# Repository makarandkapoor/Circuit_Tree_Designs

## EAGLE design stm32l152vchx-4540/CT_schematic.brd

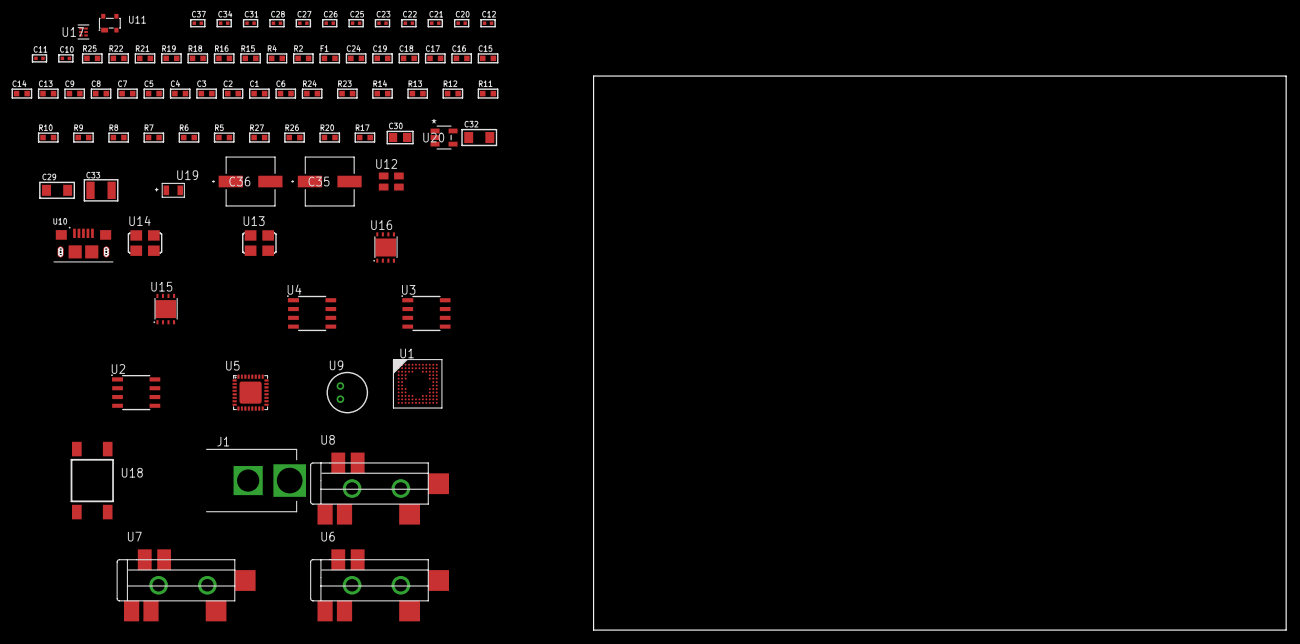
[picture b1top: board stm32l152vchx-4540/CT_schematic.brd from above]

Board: 2 copper layers, 84 parts (0 on the bottom side), 59 nets, no tracks yet.

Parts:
C1, C2, C3, C4, C5, C7: 1e-07; C0603
C6: 4.7e-06; C0603
C8: 1e-08; C0603
C9, C13, C14, C15, C16, C17, C18, C19, C24: 1e-06; C0603
C10, C11, C12, C25, C26, C27, C28, C31, C37: 1e-08; C0402
C20, C21, C22, C23, C34: 1e-07; C0402
C29, C32: 1e-05; C1206
C30: 1e-05; C0805
C33: 1e-05; C1210
C35, C36: 0.0001; EXV-9H
F1: 240.0; L0603
J1: PJ-037B; PJ-037B_PACKAGE
R2, R19, R22: 1000.0; R0603
R4: 4700.0; R0603
R5, R6, R7, R8, R9, R10, R11, R12, R13, R14, R23, R24: 10000.0; R0603
R15, R16: 1270.0; R0603
R17, R20: 100000.0; R0603
R18: 200.0; R0603
R21: 2231.0; R0603
R25: 9100.0; R0603
R26: 680000.0; R0603
R27: 120000.0; R0603
U1: STM32L152VCH6; UFBGA100
U2: AT25040B-SSHL-T; SOIC-8
U3: AT25080B-SSHL-T; SOIC-8
U4: AT25320B-SSHL-T; SOIC-8
U5: SGTL5000XNAA3; QFN-32
U6, U7, U8: SJ-43515TS-SMT-TR
U9: WM-64PCT; WM-64PC
U10: 10118193-0001LF; FCI_10118193-0001LF
U11: prtr5v0u2ax; SOT143B
U12: ASEK-32.768KHz-ECST; ASEK
U13: ASFL-24.57MHZ-NCS; ASFL1
U14: ASFL1-25MHZ-NCS; ASFL1
U15, U16: LP3878SDX-ADJ/NOPB; WSON-8
U17: TPS3895ADRYR; SON-6
U18: 4-1437565-2; SW_4-1437565-2
U19: Q65110A2395; LGM67K-G1J2-24-Z
U20: nc7sz125m5x; NC7SZ125M5X

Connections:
CLK_U1_D1: U1.D1, U12.3
CLK_U1_F1: U1.F1, U14.3
CLK_U5_21: U5.21, U13.3
GND: C1.2, C2.2, C3.2, C4.2, C5.2, C6.2, C7.2, C8.2, C9.2, C10.2, C11.2, C12.2, C20.2, C21.2, C22.2, C23.2, C24.2, C25.2, C26.2, C27.2, C28.2, C29.2, C30.2, C31.2, C32.2, C33.2, C34.2, C35.2, C36.2, C37.2, J1.2, R2.2, R5.2, R16.2, R19.2, R22.2, R25.2, R27.2, U1.D3, U1.E3, U1.F2, U1.F11, U1.F12, U1.J1, U1.K1, U2.4, U3.4, U4.4, U5.1, U5.3, U5.7, U5.EXP, U7.1, U8.1, U9.2, U10.5, U10.6, U10.7, U10.8, U10.9, U11.1, U12.2, U13.2, U14.2, U15.3, U15.PAD, U16.3, U16.PAD, U17.2, U19.C, U20.1, U20.3
NET_U1_A4: R5.1, U1.A4
NET_U1_E2: C7.1, U1.E2
NET_U1_H2: R4.1, U1.H2, U20.4
NET_U1_M1: C8.1, C9.1, F1.1, U1.L1, U1.M1
NET_U1_M12: U18.3, U18.4
NET_U2_3: R6.1, U2.3
NET_U2_7: R8.1, U2.7
NET_U3_3: R9.1, U3.3
NET_U3_7: R11.1, U3.7
NET_U4_3: R12.1, U4.3
NET_U4_7: R14.1, U4.7
NET_U5_10: C23.1, U5.10
NET_U5_29: R15.1, U5.29
NET_U5_31: R16.1, U5.31
NET_U6_1: U5.4, U6.1
NET_U6_2: U5.2, U6.2
NET_U6_5: U5.6, U6.5
NET_U7_2: C14.1, U7.2
NET_U7_5: C13.1, U7.5
NET_U8_2: C16.1, C17.1, U8.2
NET_U8_5: C15.1, U8.5
NET_U8_13: C16.2, C17.2
NET_U9_1: C18.1, C19.1, C24.1, U5.16, U9.1
NET_U9_15: C18.2, C19.2
NET_U11_4: U10.1, U11.4
NET_U15_1: C28.1, U15.1
NET_U15_6: R18.2, R19.1, U15.6
NET_U15_8: R17.1, U15.8
NET_U16_1: C31.1, U16.1
NET_U16_6: R21.2, R22.1, U16.6
NET_U16_8: R20.1, U16.8
NET_U17_1: R24.1, R25.1, U17.1
NET_U17_3: R26.2, R27.1, U17.3
NET_U17_4: R23.1, U17.4, U20.2
NET_U18_1: R2.1, U18.1, U18.2
PROC_I2S2_CK: U1.K12, U5.24
PROC_I2S2_SD: U1.K10, U5.26
PROC_I2S2_WS: U1.L12, U5.23
PROC_SPI1_MISO: U1.L4, U4.2
PROC_SPI1_MOSI: U1.C5, U4.5
PROC_SPI1_NSS: R13.1, U1.L9, U4.1
PROC_SPI1_SCK: U1.K4, U4.6
PROC_SPI2_MISO: U1.B8, U3.2
PROC_SPI2_MOSI: U1.B7, U3.5
PROC_SPI2_NSS: R10.1, U1.C9, U3.1
PROC_SPI2_SCK: U1.B9, U3.6
PROC_SPI3_MISO: U1.A7, U2.2
PROC_SPI3_MOSI: U1.B10, U2.5
PROC_SPI3_NSS: R7.1, U1.A9, U2.1
PROC_SPI3_SCK: U1.A8, U2.6
PROC_USB_DM: U1.B12, U10.2, U11.3
PROC_USB_DP: U1.A12, U10.3, U11.2
VCC_S1_10V0: C29.1, C32.1, C35.1, C36.1, J1.1, R17.2, R20.2, U15.4, U16.4
VCC_TIER1_1V2: C20.1, C30.1, R18.1, U5.30, U15.5
VCC_TIER1_3V3: C1.1, C2.1, C3.1, C4.1, C5.1, C6.1, C10.1, C11.1, C12.1, C21.1, C22.1, C25.1, C26.1, C27.1, C33.1, C34.1, C37.1, F1.2, R4.2, R6.2, R7.2, R8.2, R9.2, R10.2, R11.2, R12.2, R13.2, R14.2, R15.2, R21.1, R23.2, R24.2, R26.1, U1.C4, U1.G2, U1.G11, U1.G12, U1.H3, U2.8, U3.8, U4.8, U5.5, U5.20, U12.4, U13.4, U14.4, U16.5, U17.6, U20.5

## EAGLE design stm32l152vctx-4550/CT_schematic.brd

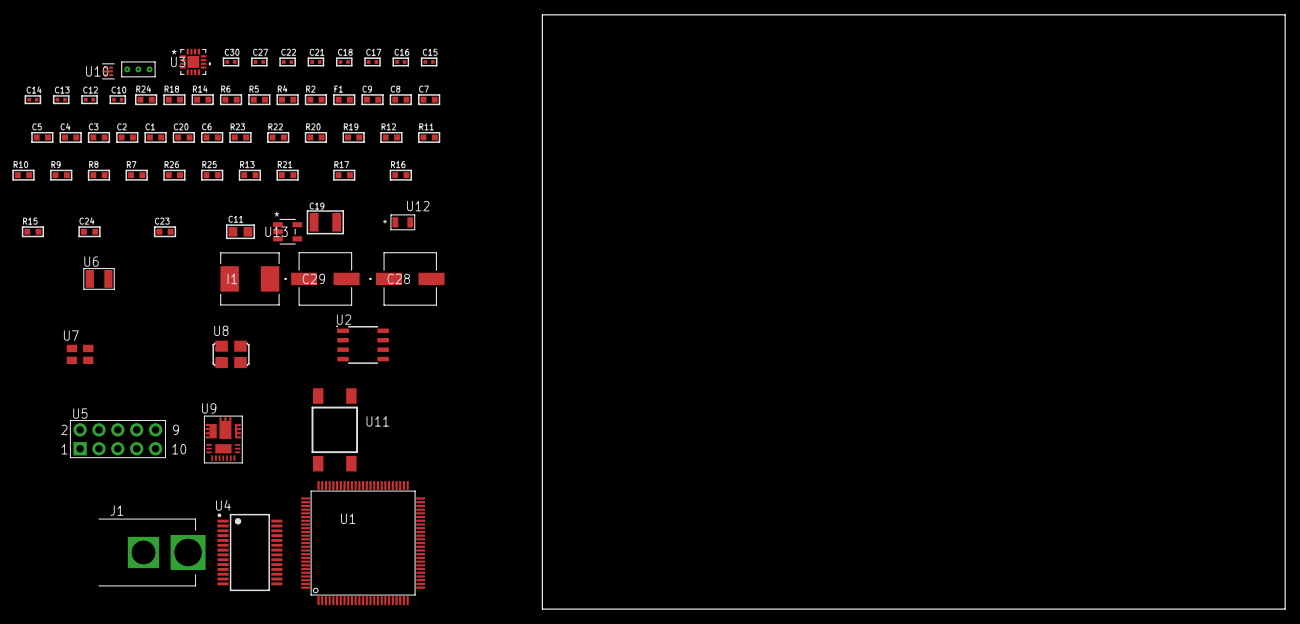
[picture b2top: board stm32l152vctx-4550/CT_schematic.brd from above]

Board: 2 copper layers, 100.0 x 80.0 mm, 69 parts (0 on the bottom side), 53 nets, no tracks yet.

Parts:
C1, C2, C3, C4, C5, C7: 1e-07; C0603
C6: 4.7e-06; C0603
C8: 1e-08; C0603
C9: 1e-06; C0603
C10, C17, C18, C30: 1e-08; C0402
C11: 4.7e-06; C0805
C12, C13, C14, C15, C16, C21, C22, C27: 1e-07; C0402
C19: 0.0001; C1210
C20: 2.2e-06; C0603
C23: 8.6971073877236e-09; R0603
C24: 2.9649229730876e-07; R0603
C28, C29: 0.0001; EXV-9H
F1: 240.0; L0603
I1: 6.8e-07; IND25X25CZ
J1: PJ-037B; PJ-037B_PACKAGE
R2: 1000.0; R0603
R4: 4700.0; R0603
R5, R6: 2200.0; R0603
R7, R8, R9, R10, R11, R12, R22, R23: 10000.0; R0603
R13: 100000.0; R0603
R14: 0.1; R0603
R15: 4030.2416170974; R0603
R16: 719.68600305311; R0603
R17: 58.613333333333; R0603
R18: 130.0; R0603
R19: 39000.0; R0603
R20: 49900.0; R0603
R21: 5147.5789473684; R0603
R24: 9100.0; R0603
R25: 680000.0; R0603
R26: 120000.0; R0603
U1: STM32L152VCT6; LQFP100
U2: AT25080B-SSHL-T; SOIC-8
U3: M41T65Q6F; M41T65_QFN-16
U4: ST3241EBPR; SSOP-28
U5: HTSS-105-01-G-D
U6: ABS07-32.768KHZ-7-T
U7: ASEK-32.768KHz-ECST; ASEK
U8: ASFL1-25MHZ-NCS; ASFL1
U9: IR3899MTR1PBF
U10: TPS3895ADRYR; SON-6
U11: 4-1437565-2; SW_4-1437565-2
U12: Q65110A2395; LGM67K-G1J2-24-Z
U13: nc7sz125m5x; NC7SZ125M5X
U14: Dummy; DUMMY_PACKAGE_141

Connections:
CLK_CRYSTAL_U3_1: U3.1, U6.1
CLK_CRYSTAL_U3_2: U3.2, U6.2
CLK_U1_8: U1.8, U7.3
CLK_U1_12: U1.12, U8.3
GND: C1.2, C2.2, C3.2, C4.2, C5.2, C6.2, C7.2, C8.2, C9.2, C10.2, C11.2, C12.2, C15.2, C16.2, C17.2, C18.2, C20.2, C21.2, C22.2, C27.2, C28.2, C29.2, C30.2, J1.2, R2.2, R7.2, R14.1, R14.2, R16.2, R19.2, R21.2, R24.2, R26.2, U1.10, U1.19, U1.20, U1.27, U1.49, U1.74, U1.99, U2.4, U3.3, U3.5, U3.17, U4.23, U4.25, U5.9, U7.2, U8.2, U9.4, U9.11, U9.17, U10.2, U12.C, U13.1, U13.3, U14.1
NET_U1_6: C7.1, U1.6
NET_U1_14: R4.1, U1.14, U13.4
NET_U1_22: C8.1, C9.1, F1.1, U1.21, U1.22
NET_U1_92: R5.1, U1.92, U3.10
NET_U1_93: R6.1, U1.93, U3.9
NET_U1_94: R7.1, U1.94
NET_U1_98: U11.3, U11.4
NET_U2_3: R8.1, U2.3
NET_U2_7: R10.1, U2.7
NET_U3_4: R11.1, U3.4
NET_U3_11: R12.1, U3.11
NET_U4_1: C14.1, U4.1
NET_U4_2: C14.2, U4.2
NET_U4_3: C16.1, U4.3
NET_U4_22: R13.1, U4.22
NET_U4_24: C13.2, U4.24
NET_U4_27: C15.1, U4.27
NET_U4_28: C13.1, U4.28
NET_U5_3: U4.4, U5.3
NET_U5_4: U4.5, U5.4
NET_U5_5: U4.9, U5.5
NET_U5_6: U4.10, U5.6
NET_U9_1: C23.1, R15.1, R16.1, R17.1, R18.1, U9.1, U9.8
NET_U9_2: C22.1, U9.2
NET_U9_3: C23.2, C24.1, C24.2, U9.3
NET_U9_5: R19.1, U9.5
NET_U9_10: C20.1, U9.10
NET_U9_12: C19.1, I1.1, U9.12
NET_U9_14: C19.2, U9.14
NET_U9_15: R20.1, R21.1, U9.15
NET_U9_ATNET_3: I1.2, R15.2
NET_U9_ATNET_4: C24.2, R17.2
NET_U10_1: R23.1, R24.1, U10.1
NET_U10_3: R25.2, R26.1, U10.3
NET_U10_4: R22.1, U10.4, U13.2
NET_U11_1: R2.1, U11.1, U11.2
PROC_PE2: U1.1, U14.2
PROC_PE3: U1.2, U14.3
PROC_SPI1_MISO: U1.31, U2.2
PROC_SPI1_MOSI: U1.32, U2.5
PROC_SPI1_NSS: R9.1, U1.29, U2.1
PROC_SPI1_SCK: U1.30, U2.6
PROC_USART1_CTS: U1.70, U4.13
PROC_USART1_RTS: U1.71, U4.18
PROC_USART1_RX: U1.69, U4.19
PROC_USART1_TX: U1.68, U4.14
VCC_S1_16V8: C21.1, C28.1, C29.1, J1.1, R20.2, U9.9
VCC_TIER1_3V3: C1.1, C2.1, C3.1, C4.1, C5.1, C6.1, C10.1, C11.1, C12.1, C17.1, C18.1, C27.1, C30.1, F1.2, I1.2, R4.2, R5.2, R6.2, R8.2, R9.2, R10.2, R11.2, R12.2, R13.2, R15.2, R22.2, R23.2, R25.1, U1.11, U1.28, U1.50, U1.75, U1.100, U2.8, U3.14, U4.26, U7.4, U8.4, U10.6, U13.5

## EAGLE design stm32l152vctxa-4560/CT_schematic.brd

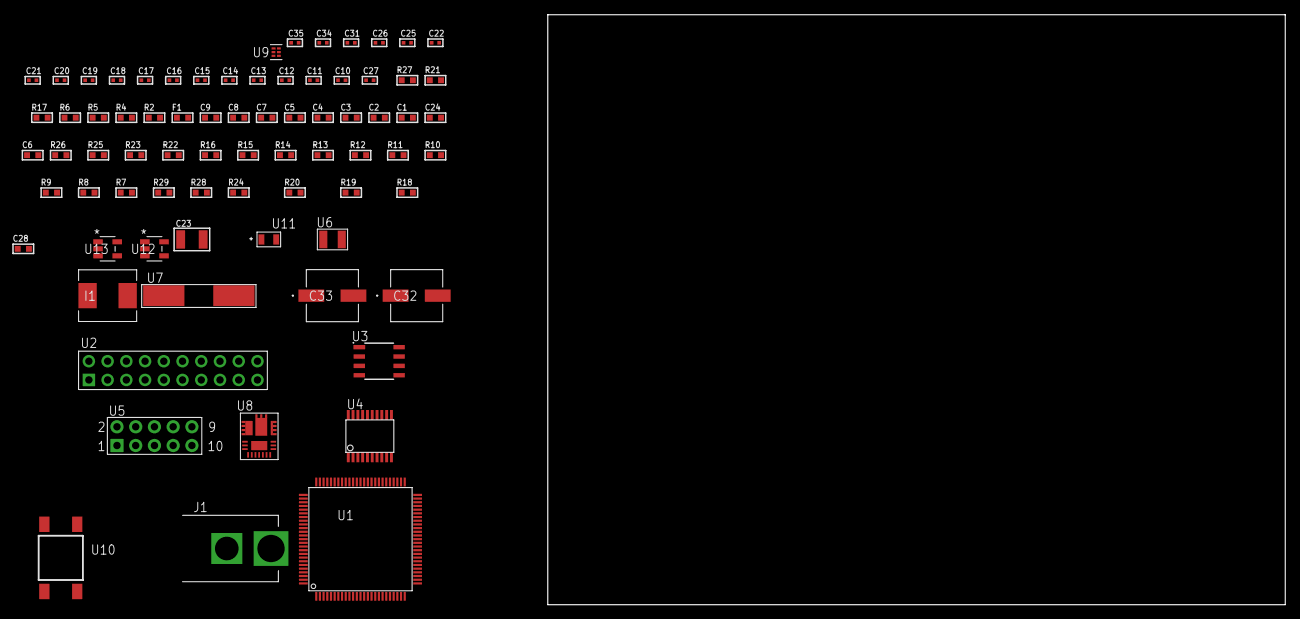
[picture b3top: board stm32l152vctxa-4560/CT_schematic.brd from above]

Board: 2 copper layers, 100.0 x 80.0 mm, 76 parts (0 on the bottom side), 52 nets, no tracks yet.

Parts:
C1, C2, C3, C4, C5, C7: 1e-07; C0603
C6: 4.7e-06; C0603
C8: 1e-08; C0603
C9: 1e-06; C0603
C10, C11, C12, C13: 1e-11; C0402
C14, C15, C17, C18, C19, C20, C21, C22, C25, C26, C31: 1e-07; C0402
C16, C34, C35: 1e-08; C0402
C23: 0.0001; C1210
C24: 2.2e-06; C0603
C27: 8.2e-09; C0402
C28: 2.724074888439e-07; R0603
C32, C33: 0.0001; EXV-9H
F1: 240.0; L0603
I1: 6.8e-07; IND25X25CZ
J1: PJ-037B; PJ-037B_PACKAGE
R2: 1000.0; R0603
R4: 4700.0; R0603
R5, R6: 2200.0; R0603
R7, R8, R9, R10, R11, R12, R13, R14, R15, R16, R25, R26: 10000.0; R0603
R17: 0.1; R0603
R18: 4030.2416170974; R0603
R19: 719.68600305311; R0603
R20: 63.795609756098; R0603
R21: 130.0; R0603
R22: 39000.0; R0603
R23: 49900.0; R0603
R24: 5286.7027027027; R0603
R27: 9100.0; R0603
R28: 680000.0; R0603
R29: 120000.0; R0603
U1: STM32L152VCT6A; LQFP100
U2: TST-110-05-T-D-RA
U3: 24AA1025T-I/SN; SOIC-8
U4: SP3203ECY-L/TR; TSSOP20-I
U5: HTSS-105-01-G-D
U6: ABS07-32.768KHZ-7-T
U7: ABLS-25.000MHZ-B2F-T
U8: IR3899MTR1PBF
U9: TPS3895ADRYR; SON-6
U10: 4-1437565-2; SW_4-1437565-2
U11: Q65110A2395; LGM67K-G1J2-24-Z
U12, U13: nc7sz125m5x; NC7SZ125M5X

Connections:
CLK_CRYSTAL_U1_8: C10.1, U1.8, U6.1
CLK_CRYSTAL_U1_9: C11.1, U1.9, U6.2
CLK_CRYSTAL_U1_12: C12.1, U1.12, U7.1
CLK_CRYSTAL_U1_13: C13.1, U1.13, U7.2
GND: C1.2, C2.2, C3.2, C4.2, C5.2, C6.2, C7.2, C8.2, C9.2, C10.2, C11.2, C12.2, C13.2, C14.2, C15.2, C16.2, C17.2, C18.2, C21.2, C22.2, C24.2, C25.2, C26.2, C31.2, C32.2, C33.2, C34.2, C35.2, J1.2, R2.2, R7.2, R13.2, R16.2, R17.1, R17.2, R19.2, R22.2, R24.2, R27.2, R29.2, U1.10, U1.19, U1.20, U1.27, U1.49, U1.74, U1.99, U2.4, U2.6, U2.8, U2.10, U2.12, U2.14, U2.16, U2.18, U2.20, U3.4, U3.7, U4.18, U5.9, U8.4, U8.11, U8.17, U9.2, U11.C, U12.2, U12.3, U13.1, U13.3
NET_U1_6: C7.1, U1.6
NET_U1_14: R4.1, U1.14, U13.4
NET_U1_22: C8.1, C9.1, F1.1, U1.21, U1.22
NET_U1_92: R5.1, U1.92, U3.6
NET_U1_93: R6.1, U1.93, U3.5
NET_U1_94: R7.1, U1.94
NET_U1_98: U10.3, U10.4
NET_U2_19: R13.1, U2.19
NET_U3_1: R15.1, U3.1
NET_U3_2: R16.1, U3.2
NET_U3_3: R14.1, U3.3
NET_U4_1: C19.1, U4.1
NET_U4_2: C21.1, U4.2
NET_U4_3: C19.2, U4.3
NET_U4_4: C20.1, U4.4
NET_U4_5: C20.2, U4.5
NET_U4_6: C22.1, U4.6
NET_U5_3: U4.14, U5.3
NET_U5_4: U4.13, U5.4
NET_U5_5: U4.17, U5.5
NET_U5_6: U4.16, U5.6
NET_U8_1: C27.1, R18.1, R19.1, R20.1, R21.1, U8.1, U8.8
NET_U8_2: C26.1, U8.2
NET_U8_3: C27.2, C28.1, C28.2, U8.3
NET_U8_5: R22.1, U8.5
NET_U8_10: C24.1, U8.10
NET_U8_12: C23.1, I1.1, U8.12
NET_U8_14: C23.2, U8.14
NET_U8_15: R23.1, R24.1, U8.15
NET_U8_ATNET_3: I1.2, R18.2
NET_U8_ATNET_4: C28.2, R20.2
NET_U9_1: R26.1, R27.1, U9.1
NET_U9_3: R28.2, R29.1, U9.3
NET_U9_4: R25.1, U9.4, U12.4, U13.2
NET_U10_1: R2.1, U10.1, U10.2
PROC_SYS_JTCK_SWCLK: R11.1, U1.76, U2.9
PROC_SYS_JTDI: R9.1, U1.77, U2.5
PROC_SYS_JTDO_TRACESWO: U1.89, U2.13
PROC_SYS_JTMS_SWDIO: R10.1, U1.72, U2.7
PROC_SYS_JTRST: R8.1, U1.90, U2.3
PROC_USART1_CTS: U1.70, U4.8
PROC_USART1_RTS: U1.71, U4.10
PROC_USART1_RX: U1.69, U4.11
PROC_USART1_TX: U1.68, U4.7
RST_OUT_U2_SRESET_B: R12.1, U2.15, U12.1
VCC_S1_16V4: C25.1, C32.1, C33.1, J1.1, R23.2, U8.9
VCC_TIER1_3V3: C1.1, C2.1, C3.1, C4.1, C5.1, C6.1, C14.1, C15.1, C16.1, C17.1, C18.1, C31.1, C34.1, C35.1, F1.2, I1.2, R4.2, R5.2, R6.2, R8.2, R9.2, R10.2, R11.2, R12.2, R14.2, R15.2, R18.2, R25.2, R26.2, R28.1, U1.11, U1.28, U1.50, U1.75, U1.100, U2.1, U2.2, U3.8, U4.12, U4.19, U9.6, U12.5, U13.5

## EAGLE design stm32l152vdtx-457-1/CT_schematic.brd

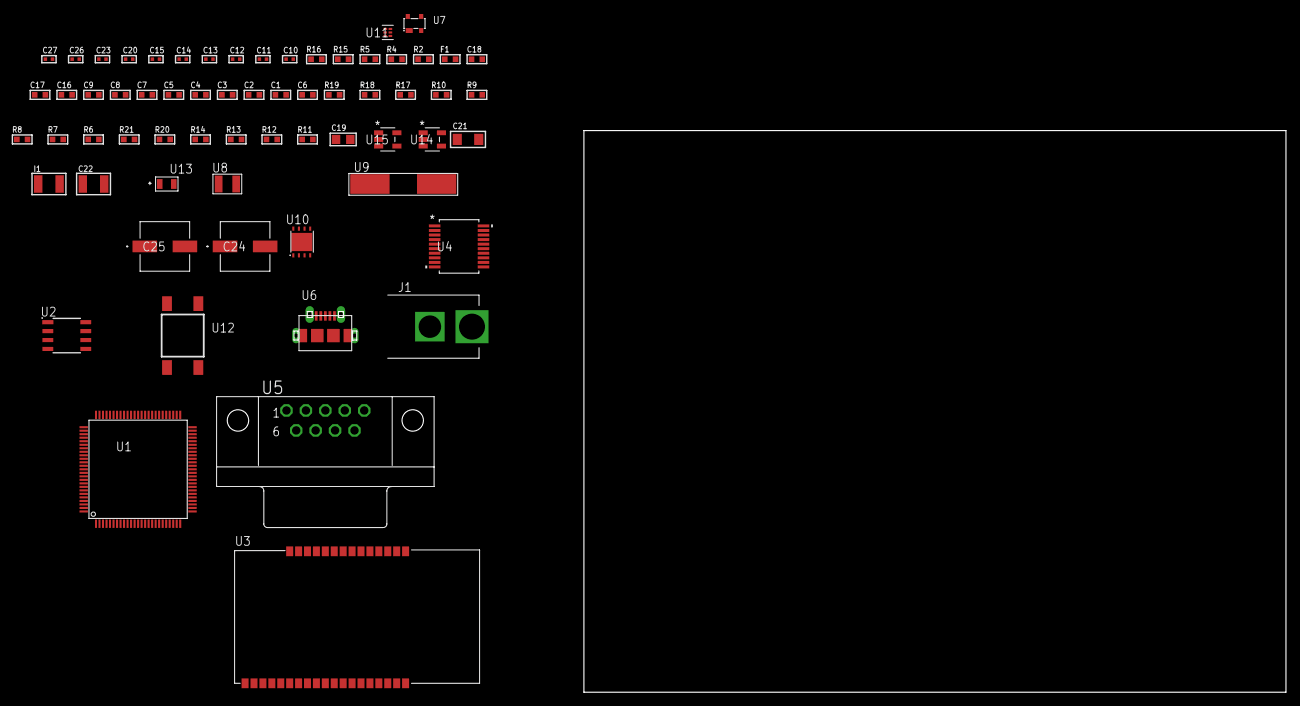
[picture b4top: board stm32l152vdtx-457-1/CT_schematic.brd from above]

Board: 2 copper layers, 64 parts (0 on the bottom side), 46 nets, no tracks yet.

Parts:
C1, C2, C3, C4, C5, C7: 1e-07; C0603
C6: 4.7e-06; C0603
C8: 1e-08; C0603
C9, C16, C17, C18: 1e-06; C0603
C10, C11, C12, C13: 1e-11; C0402
C14, C20, C26, C27: 1e-08; C0402
C15, C23: 1e-07; C0402
C19: 4.7e-06; C0805
C21: 1e-05; C1206
C22: 1e-05; C1210
C24, C25: 0.0001; EXV-9H
F1: 240.0; L0603
I1: 1.5e-05; L1210
J1: PJ-037B; PJ-037B_PACKAGE
R2, R16: 1000.0; R0603
R4, R5: 4700.0; R0603
R6, R7, R8, R9, R10, R17, R18: 10000.0; R0603
R11, R12, R13, R14: 100000.0; R0603
R15: 1500.0; R0603
R19: 18000.0; R0603
R20: 470000.0; R0603
R21: 120000.0; R0603
U1: STM32L152VDT6; LQFP100
U2: AT25080B-SSHL-T; SOIC-8
U3: ETRX3587
U4: MAX3218EAP+T; SSOP-20
U5: 182-009-113R531; 182-009-MALE
U6: 47590-0001; MICRO_USB_AB
U7: prtr5v0u2ax; SOT143B
U8: ABS07-32.768KHZ-7-T
U9: ABLS-25.000MHZ-B2F-T
U10: LP3878SDX-ADJ/NOPB; WSON-8
U11: TPS3895ADRYR; SON-6
U12: 4-1437565-2; SW_4-1437565-2
U13: Q65110A2395; LGM67K-G1J2-24-Z
U14, U15: nc7sz125m5x; NC7SZ125M5X

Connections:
CLK_CRYSTAL_U1_8: C10.1, U1.8, U8.1
CLK_CRYSTAL_U1_9: C11.1, U1.9, U8.2
CLK_CRYSTAL_U1_12: C12.1, U1.12, U9.1
CLK_CRYSTAL_U1_13: C13.1, U1.13, U9.2
GND: C1.2, C2.2, C3.2, C4.2, C5.2, C6.2, C7.2, C8.2, C9.2, C10.2, C11.2, C12.2, C13.2, C14.2, C15.2, C16.2, C17.2, C18.2, C20.2, C21.2, C22.2, C23.2, C24.2, C25.2, C26.2, C27.2, J1.2, R2.2, R6.2, R10.2, R16.2, R19.2, R21.2, U1.10, U1.19, U1.20, U1.27, U1.49, U1.74, U1.99, U2.4, U3.1, U3.13, U3.19, U3.20, U3.31, U3.33, U4.5, U4.17, U4.20, U5.5, U6.5, U6.6, U6.7, U6.8, U6.9, U7.1, U10.3, U10.PAD, U11.2, U13.C, U14.1, U14.3, U15.1, U15.3
NET_U1_6: C7.1, U1.6
NET_U1_14: R5.1, U1.14, U15.4
NET_U1_22: C8.1, C9.1, F1.1, U1.21, U1.22
NET_U1_94: R6.1, U1.94
NET_U1_98: U12.3, U12.4
NET_U2_3: R7.1, U2.3
NET_U2_7: R9.1, U2.7
NET_U3_7: R4.1, U3.7, U14.4
NET_U3_21: R10.1, U3.21
NET_U4_1: I1.1, U4.1
NET_U4_2: R11.1, U4.2
NET_U4_3: R12.1, U4.3
NET_U4_4: R13.1, U4.4
NET_U4_15: C18.1, U4.15
NET_U4_16: C19.2, U4.16
NET_U4_18: C19.1, U4.18
NET_U4_19: C17.1, U4.19
NET_U5_2: U4.12, U5.2
NET_U5_3: U4.14, U5.3
NET_U5_7: U4.11, U5.7
NET_U5_8: U4.13, U5.8
NET_U7_4: U6.1, U7.4
NET_U10_1: C20.1, U10.1
NET_U10_6: R15.2, R16.1, U10.6
NET_U10_8: R14.1, U10.8
NET_U11_1: R18.1, R19.1, U11.1
NET_U11_3: R20.2, R21.1, U11.3
NET_U11_4: R17.1, U11.4, U14.2, U15.2
NET_U12_1: R2.1, U12.1, U12.2
PROC_SPI1_MISO: U1.31, U2.2
PROC_SPI1_MOSI: U1.32, U2.5
PROC_SPI1_NSS: R8.1, U1.29, U2.1
PROC_SPI1_SCK: U1.30, U2.6
PROC_UART4_RX: U1.79, U3.17
PROC_UART4_TX: U1.78, U3.18
PROC_UART5_RX: U1.83, U4.9
PROC_UART5_TX: U1.80, U4.7
PROC_USB_DM: U1.70, U6.2, U7.3
PROC_USB_DP: U1.71, U6.3, U7.2
VCC_S1_11V1: C21.1, C24.1, C25.1, J1.1, R14.2, U10.4
VCC_TIER1_2V5: C1.1, C2.1, C3.1, C4.1, C5.1, C6.1, C14.1, C15.1, C16.1, C22.1, C23.1, C26.1, C27.1, F1.2, I1.2, R4.2, R5.2, R7.2, R8.2, R9.2, R11.2, R12.2, R13.2, R15.1, R17.2, R18.2, R20.1, U1.11, U1.28, U1.50, U1.75, U1.100, U2.8, U3.32, U4.6, U10.5, U11.6, U14.5, U15.5

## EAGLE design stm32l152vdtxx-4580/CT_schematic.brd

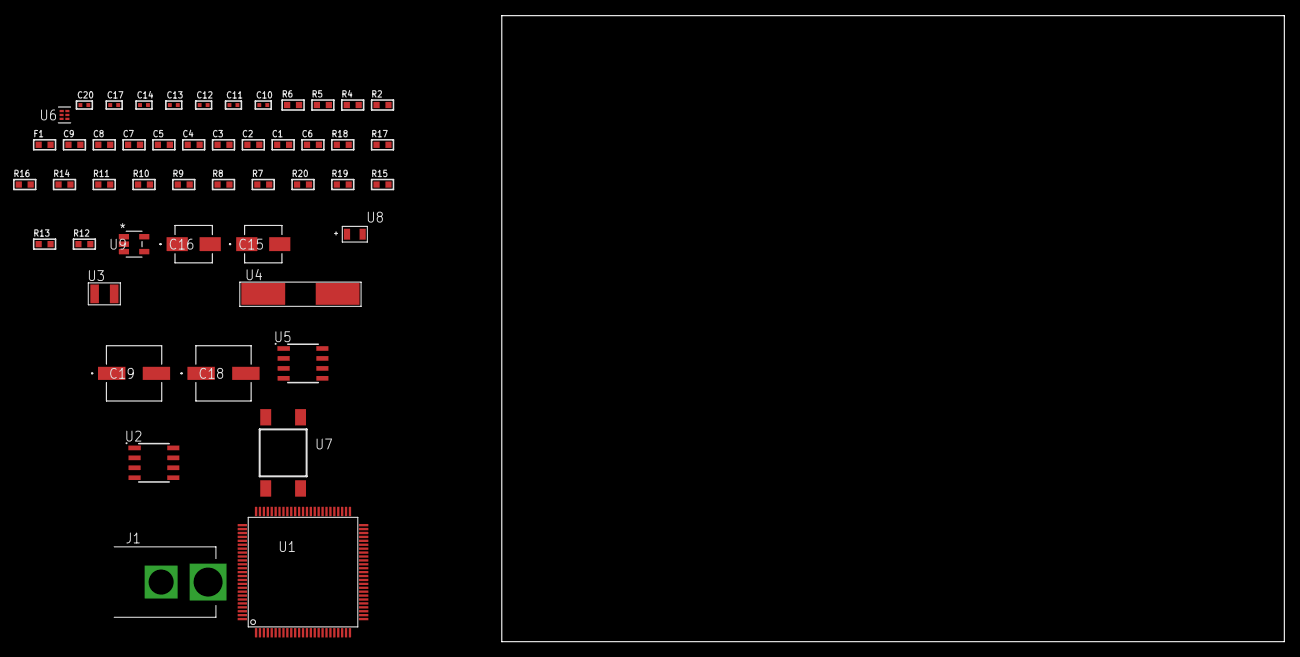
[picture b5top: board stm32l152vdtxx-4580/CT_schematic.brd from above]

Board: 2 copper layers, 100.0 x 80.0 mm, 49 parts (0 on the bottom side), 25 nets, no tracks yet.

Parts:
C1, C2, C3, C4, C5, C7: 1e-07; C0603
C6: 4.7e-06; C0603
C8: 1e-08; C0603
C9: 1e-06; C0603
C10, C11, C12, C13: 1e-11; C0402
C14, C20: 1e-08; C0402
C15: 1e-06; EXV-9B
C16: 2.2e-06; EXV-9B
C17: 1e-07; C0402
C18, C19: 0.0001; EXV-9H
F1: 240.0; L0603
J1: PJ-037B; PJ-037B_PACKAGE
R2: 1000.0; R0603
R4: 4700.0; R0603
R5, R6: 2200.0; R0603
R7, R8, R9, R10, R11, R16, R17: 10000.0; R0603
R12, R13, R15: 100000.0; R0603
R14: 47000.0; R0603
R18: 82000.0; R0603
R19: 300000.0; R0603
R20: 120000.0; R0603
U1: STM32L152VDT6X; LQFP100
U2: AT24C02D-SSHM-T; AT24C02D
U3: ABS07-32.768KHZ-7-T
U4: ABLS-25.000MHZ-B2F-T
U5: LP2954AIMX/NOPB; LP2954
U6: TPS3895ADRYR; SON-6
U7: 4-1437565-2; SW_4-1437565-2
U8: Q65110A2395; LGM67K-G1J2-24-Z
U9: nc7sz125m5x; NC7SZ125M5X

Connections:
CLK_CRYSTAL_U1_8: C10.1, U1.8, U3.1
CLK_CRYSTAL_U1_9: C11.1, U1.9, U3.2
CLK_CRYSTAL_U1_12: C12.1, U1.12, U4.1
CLK_CRYSTAL_U1_13: C13.1, U1.13, U4.2
GND: C1.2, C2.2, C3.2, C4.2, C5.2, C6.2, C7.2, C8.2, C9.2, C10.2, C11.2, C12.2, C13.2, C14.2, C15.2, C16.2, C17.2, C18.2, C19.2, C20.2, J1.2, R2.2, R7.2, R8.2, R10.2, R11.2, R15.2, R18.2, R20.2, U1.10, U1.19, U1.20, U1.27, U1.49, U1.74, U1.99, U2.4, U5.4, U6.2, U8.C, U9.1, U9.3
NET_U1_6: C7.1, U1.6
NET_U1_14: R4.1, U1.14, U9.4
NET_U1_22: C8.1, C9.1, F1.1, U1.21, U1.22
NET_U1_92: R5.1, U1.92, U2.6
NET_U1_93: R6.1, U1.93, U2.5
NET_U1_94: R7.1, U1.94
NET_U1_98: U7.3, U7.4
NET_U2_1: R9.1, U2.1
NET_U2_2: R10.1, U2.2
NET_U2_3: R11.1, U2.3
NET_U2_7: R8.1, U2.7
NET_U5_3: R13.1, U5.3
NET_U5_5: R12.1, U5.5
NET_U5_7: R14.2, R15.1, U5.7
NET_U6_1: R17.1, R18.1, U6.1
NET_U6_3: R19.2, R20.1, U6.3
NET_U6_4: R16.1, U6.4, U9.2
NET_U7_1: R2.1, U7.1, U7.2
VCC_S1_12V3: C15.1, C18.1, C19.1, J1.1, R13.2, U5.8
VCC_TIER1_1V8: C1.1, C2.1, C3.1, C4.1, C5.1, C6.1, C14.1, C16.1, C17.1, C20.1, F1.2, R4.2, R5.2, R6.2, R9.2, R12.2, R14.1, R16.2, R17.2, R19.1, U1.11, U1.28, U1.50, U1.75, U1.100, U2.8, U5.1, U6.6, U9.5

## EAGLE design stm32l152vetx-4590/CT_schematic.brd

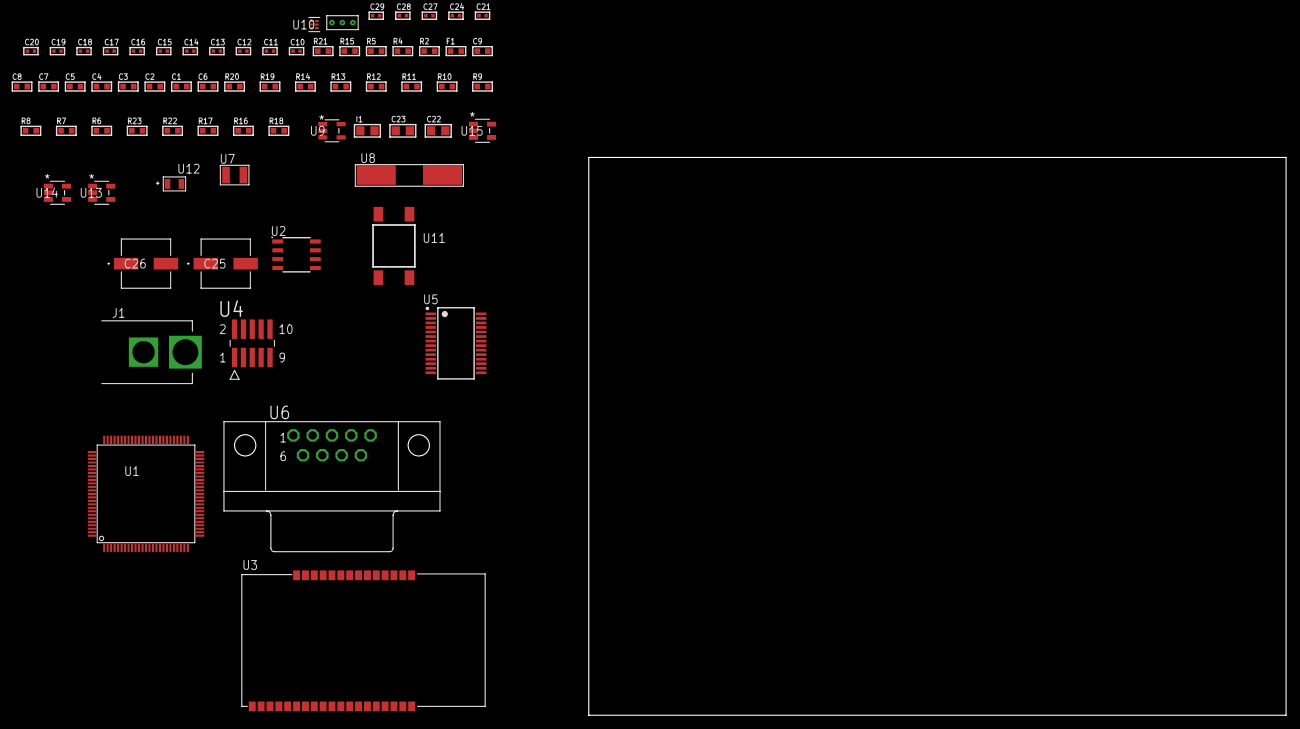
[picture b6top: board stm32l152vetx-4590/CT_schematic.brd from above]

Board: 2 copper layers, 100.0 x 80.0 mm, 69 parts (0 on the bottom side), 50 nets, no tracks yet.

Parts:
C1, C2, C3, C4, C5, C7: 1e-07; C0603
C6: 4.7e-06; C0603
C8: 1e-08; C0603
C9: 1e-06; C0603
C10, C11, C12, C13: 1e-11; C0402
C14, C27, C28, C29: 1e-08; C0402
C15, C16, C17, C18, C19, C20, C21, C24: 1e-07; C0402
C22, C23: 1e-05; C0805
C25, C26: 0.0001; EXV-9H
F1: 240.0; L0603
I1: 1e-05; L0805
J1: PJ-037B; PJ-037B_PACKAGE
R2: 1000.0; R0603
R4, R5: 4700.0; R0603
R6, R7, R8, R9, R10, R11, R12, R13, R14, R19, R20: 10000.0; R0603
R15: 5.0; R0603
R16: 100000.0; R0603
R17: 220000.0; R0603
R18: 1000000.0; R0603
R21: 9100.0; R0603
R22: 680000.0; R0603
R23: 120000.0; R0603
U1: STM32L152VET6; LQFP100
U2: AT25512N-SH-T; SOIC-8
U3: ETRX3587
U4: FTSH-105-01-L-DV-K; SAMTEC_FTSH-105-01-L-DV-K
U5: ST3241EBPR; SSOP-28
U6: 182-009-113R531; 182-009-MALE
U7: ABS07-32.768KHZ-7-T
U8: ABLS-25.000MHZ-B2F-T
U9: ltc3406es5; TSOT-23-5
U10: TPS3895ADRYR; SON-6
U11: 4-1437565-2; SW_4-1437565-2
U12: Q65110A2395; LGM67K-G1J2-24-Z
U13, U14, U15: nc7sz125m5x; NC7SZ125M5X
U16: Dummy; DUMMY_PACKAGE_146

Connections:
CLK_CRYSTAL_U1_8: C10.1, U1.8, U7.1
CLK_CRYSTAL_U1_9: C11.1, U1.9, U7.2
CLK_CRYSTAL_U1_12: C12.1, U1.12, U8.1
CLK_CRYSTAL_U1_13: C13.1, U1.13, U8.2
GND: C1.2, C2.2, C3.2, C4.2, C5.2, C6.2, C7.2, C8.2, C9.2, C10.2, C11.2, C12.2, C13.2, C14.2, C15.2, C16.2, C17.2, C20.2, C21.2, C22.2, C23.1, C23.2, C24.2, C25.2, C26.2, C27.2, C28.2, C29.2, J1.2, R2.2, R6.2, R10.2, R14.2, R15.2, R17.2, R21.2, R23.2, U1.10, U1.19, U1.20, U1.27, U1.49, U1.74, U1.99, U2.4, U3.1, U3.13, U3.19, U3.20, U3.31, U3.33, U4.3, U4.5, U5.23, U5.25, U6.5, U9.2, U10.2, U12.C, U13.2, U13.3, U14.1, U14.3, U15.1, U15.3, U16.1
NET_U1_6: C7.1, U1.6
NET_U1_14: R5.1, U1.14, U15.4
NET_U1_22: C8.1, C9.1, F1.1, U1.21, U1.22
NET_U1_94: R6.1, U1.94
NET_U1_98: U11.3, U11.4
NET_U2_3: R7.1, U2.3
NET_U2_7: R9.1, U2.7
NET_U3_7: R4.1, U3.7, U14.4
NET_U3_21: R10.1, U3.21
NET_U4_9: R15.1, U4.9
NET_U5_1: C19.1, U5.1
NET_U5_2: C19.2, U5.2
NET_U5_3: C21.1, U5.3
NET_U5_22: R16.1, U5.22
NET_U5_24: C18.2, U5.24
NET_U5_27: C20.1, U5.27
NET_U5_28: C18.1, U5.28
NET_U6_2: U5.4, U6.2
NET_U6_3: U5.9, U6.3
NET_U6_7: U5.5, U6.7
NET_U6_8: U5.10, U6.8
NET_U9_3: I1.1, U9.3
NET_U9_5: R17.1, R18.1, U9.5
NET_U9_ATNET_3: I1.2, R18.2
NET_U10_1: R20.1, R21.1, U10.1
NET_U10_3: R22.2, R23.1, U10.3
NET_U10_4: R19.1, U10.4, U13.4, U14.2, U15.2
NET_U11_1: R2.1, U11.1, U11.2
PROC_SPI1_MISO: U1.31, U2.2
PROC_SPI1_MOSI: U1.32, U2.5
PROC_SPI1_NSS: R8.1, U1.29, U2.1
PROC_SPI1_SCK: U1.30, U2.6
PROC_SYS_JTCK_SWCLK: R14.1, U1.76, U4.4
PROC_SYS_JTDI: R12.1, U1.77, U4.8
PROC_SYS_JTDO_TRACESWO: U1.89, U4.6
PROC_SYS_JTMS_SWDIO: R13.1, U1.72, U4.2
PROC_TIM2_CH1: U1.23, U16.3
PROC_TIM2_CH3: U1.25, U16.2
PROC_UART4_RX: U1.79, U3.17
PROC_UART4_TX: U1.78, U3.18
PROC_UART5_RX: U1.83, U5.19
PROC_UART5_TX: U1.80, U5.14
RST_OUT_U4_JTAG_RST_B: R11.1, U4.10, U13.1
VCC_S1_5V4: C22.1, C25.1, C26.1, J1.1, U9.4
VCC_TIER1_3V3: C1.1, C2.1, C3.1, C4.1, C5.1, C6.1, C14.1, C15.1, C16.1, C17.1, C23.2, C24.1, C27.1, C28.1, C29.1, F1.2, I1.2, R4.2, R5.2, R7.2, R8.2, R9.2, R11.2, R12.2, R13.2, R16.2, R18.2, R19.2, R20.2, R22.1, U1.11, U1.28, U1.50, U1.75, U1.100, U2.8, U3.32, U4.1, U5.26, U10.6, U13.5, U14.5, U15.5

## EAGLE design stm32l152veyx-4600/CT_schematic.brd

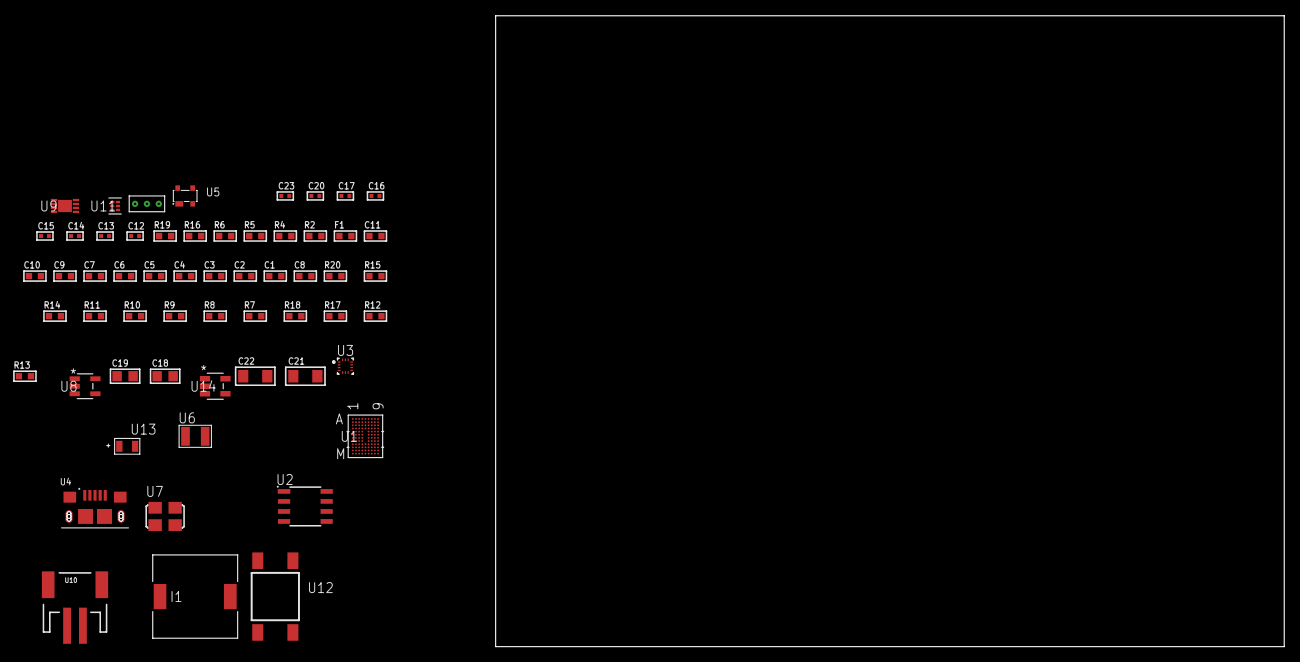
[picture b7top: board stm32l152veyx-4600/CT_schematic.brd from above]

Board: 2 copper layers, 154.3 x 80.0 mm, 58 parts (0 on the bottom side), 33 nets, no tracks yet.

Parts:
C1, C2, C3, C4, C5, C6, C7, C9: 1e-07; C0603
C8: 4.7e-06; C0603
C10: 1e-08; C0603
C11: 1e-06; C0603
C12, C13: 1e-11; C0402
C14, C17, C23: 1e-08; C0402
C15, C16, C20: 1e-07; C0402
C18, C19: 1e-05; C0805
C21, C22: 1e-05; C1206
F1: 240.0; L0603
I1: 3.8e-06; DR1040
R2: 1000.0; R0603
R4: 4700.0; R0603
R5, R6: 2200.0; R0603
R7, R8, R9, R10, R11, R14, R15, R20: 10000.0; R0603
R12: 220000.0; R0603
R13: 1000000.0; R0603
R16: 9100.0; R0603
R17: 680000.0; R0603
R18: 120000.0; R0603
R19: 2000.0; R0603
U1: STM32L152VEY6TR; WLCSP104
U2: AT25080B-SSHL-T; SOIC-8
U3: BMC150; LGA14R35P5X6_200X200X100
U4: 10118193-0001LF; FCI_10118193-0001LF
U5: prtr5v0u2ax; SOT143B
U6: ABS07-32.768KHZ-7-T
U7: ASFL1-25MHZ-NCS; ASFL1
U8: ltc3406es5; TSOT-23-5
U9: MCP73831T-2ACI/MC; DFN8_2X3MC
U10: S2B-PH-SM4-TB(LF)(SN); JST-2-SMD
U11: TPS3895ADRYR; SON-6
U12: 4-1437565-2; SW_4-1437565-2
U13: Q65110A2395; LGM67K-G1J2-24-Z
U14: nc7sz125m5x; NC7SZ125M5X
U15: Dummy; DUMMY_PACKAGE_128

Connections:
CLK_CRYSTAL_U1_D8: C12.1, U1.D8, U6.1
CLK_CRYSTAL_U1_D9: C13.1, U1.D9, U6.2
CLK_U1_F8: U1.F8, U7.3
GND: C1.2, C2.2, C3.2, C4.2, C5.2, C6.2, C7.2, C8.2, C9.2, C10.2, C11.2, C12.2, C13.2, C14.2, C15.2, C16.2, C17.2, C18.2, C19.1, C19.2, C20.2, C21.2, C22.2, C23.2, R2.2, R7.2, R12.2, R16.2, R18.2, R19.2, U1.A1, U1.C7, U1.D2, U1.E8, U1.H8, U1.J9, U1.K8, U1.L2, U1.M1, U2.4, U3.1, U3.6, U3.7, U3.9, U4.5, U4.6, U4.7, U4.8, U4.9, U5.1, U7.2, U8.2, U9.6, U9.9, U10.2, U11.2, U13.C, U14.1, U14.3, U15.1
INPUT_USBPOWER_5V: C21.1, R20.2, U4.1, U5.4, U9.1, U9.2
NET_U1_A7: R7.1, U1.A7
NET_U1_B6: R6.1, U1.B6, U3.14
NET_U1_C5: R5.1, U1.C5, U3.11
NET_U1_E7: C9.1, U1.E7
NET_U1_F7: R4.1, U1.F7, U14.4
NET_U1_G6: C10.1, C11.1, F1.1, U1.G6, U1.G7
NET_U1_M8: U12.3, U12.4
NET_U2_3: R8.1, U2.3
NET_U2_7: R10.1, U2.7
NET_U8_3: I1.1, U8.3
NET_U8_5: R12.1, R13.1, U8.5
NET_U8_ATNET_3: I1.2, R13.2
NET_U9_5: R20.1, U9.5
NET_U9_8: R19.1, U9.8
NET_U11_1: R15.1, R16.1, U11.1
NET_U11_3: R17.2, R18.1, U11.3
NET_U11_4: R14.1, U11.4, U14.2
NET_U12_1: R2.1, U12.1, U12.2
PROC_SPI1_MISO: U1.A5, U2.2
PROC_SPI1_MOSI: U1.A6, U2.5
PROC_SPI1_NSS: R9.1, U1.B1, U2.1
PROC_SPI1_SCK: U1.B5, U2.6
PROC_TIM10_CH1: U1.B7, U15.2
PROC_TIM11_CH1: U1.A8, U15.3
PROC_USB_DM: U1.E1, U4.2, U5.3
PROC_USB_DP: U1.E2, U4.3, U5.2
VCC_S1_3V7: C18.1, C22.1, U8.4, U9.3, U9.4, U10.1
VCC_TIER1_3V3: C1.1, C2.1, C3.1, C4.1, C5.1, C6.1, C7.1, C8.1, C14.1, C15.1, C16.1, C17.1, C19.2, C20.1, C23.1, F1.2, I1.2, R4.2, R5.2, R6.2, R8.2, R9.2, R10.2, R11.1, R11.2, R13.2, R14.2, R15.2, R17.1, U1.A9, U1.B8, U1.C1, U1.E9, U1.K3, U1.L8, U1.M9, U2.8, U3.8, U3.10, U3.12, U3.13, U7.4, U11.6, U14.5

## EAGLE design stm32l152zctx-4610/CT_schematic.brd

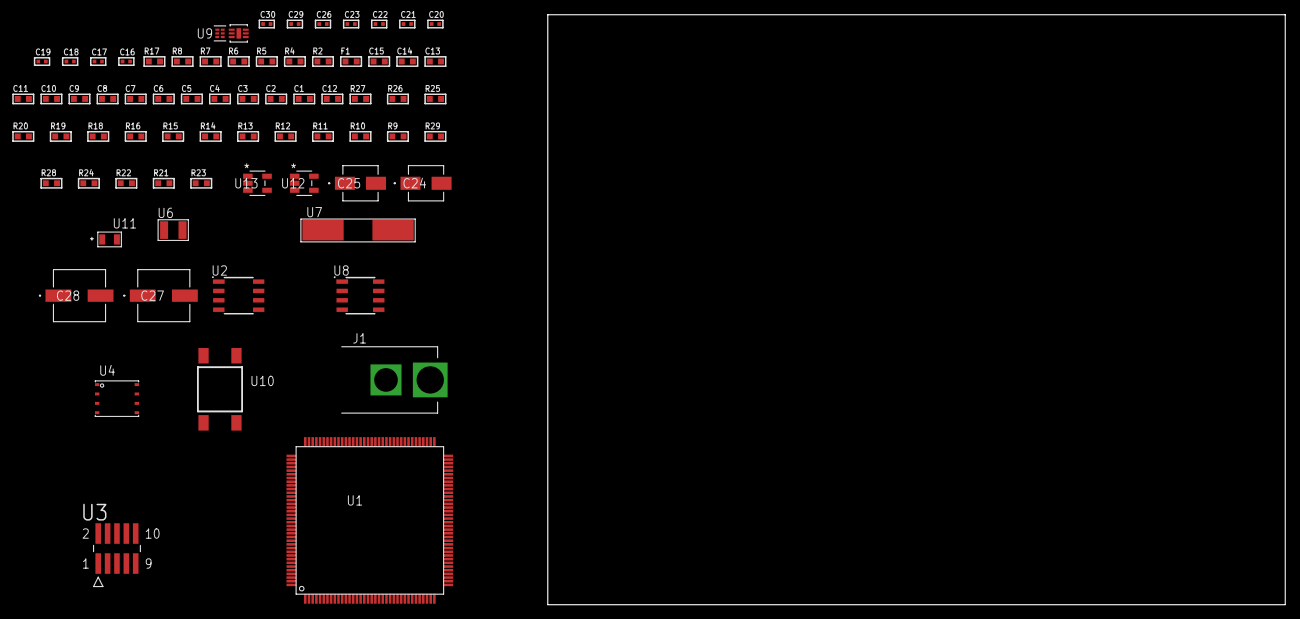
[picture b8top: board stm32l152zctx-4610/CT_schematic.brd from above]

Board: 2 copper layers, 100.0 x 80.0 mm, 72 parts (0 on the bottom side), 38 nets, no tracks yet.

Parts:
C1, C2, C3, C4, C5, C6, C7, C8, C9, C10, C11, C13: 1e-07; C0603
C12: 4.7e-06; C0603
C14: 1e-08; C0603
C15: 1e-06; C0603
C16, C17, C18, C19: 1e-11; C0402
C20, C22, C29, C30: 1e-08; C0402
C21, C23, C26: 1e-07; C0402
C24: 1e-06; EXV-9B
C25: 2.2e-06; EXV-9B
C27, C28: 0.0001; EXV-9H
F1: 240.0; L0603
J1: PJ-037B; PJ-037B_PACKAGE
R2: 1000.0; R0603
R4: 4700.0; R0603
R5, R6, R7, R8: 2200.0; R0603
R9, R10, R11, R12, R13, R14, R15, R16, R18, R19, R20, R25, R26: 10000.0; R0603
R17: 5.0; R0603
R21, R22, R24: 100000.0; R0603
R23: 101022.32; R0603
R27: 18000.0; R0603
R28: 470000.0; R0603
R29: 120000.0; R0603
U1: STM32L152ZCT6; LQFP144
U2: AT25080B-SSHL-T; SOIC-8
U3: FTSH-105-01-L-DV-K; SAMTEC_FTSH-105-01-L-DV-K
U4: 24AA512-I/MF; DFN8-S
U5: SI7006-A20-IM; DFN-6
U6: ABS07-32.768KHZ-7-T
U7: ABLS-25.000MHZ-B2F-T
U8: LP2954AIMX/NOPB; LP2954
U9: TPS3895ADRYR; SON-6
U10: 4-1437565-2; SW_4-1437565-2
U11: Q65110A2395; LGM67K-G1J2-24-Z
U12, U13: nc7sz125m5x; NC7SZ125M5X

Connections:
CLK_CRYSTAL_U1_8: C16.1, U1.8, U6.1
CLK_CRYSTAL_U1_9: C17.1, U1.9, U6.2
CLK_CRYSTAL_U1_23: C18.1, U1.23, U7.1
CLK_CRYSTAL_U1_24: C19.1, U1.24, U7.2
GND: C1.2, C2.2, C3.2, C4.2, C5.2, C6.2, C7.2, C8.2, C9.2, C10.2, C11.2, C12.2, C13.2, C14.2, C15.2, C16.2, C17.2, C18.2, C19.2, C20.2, C21.2, C22.2, C23.2, C24.2, C25.2, C26.2, C27.2, C28.2, C29.2, C30.2, J1.2, R2.2, R9.2, R16.2, R17.2, R19.2, R20.2, R24.2, R27.2, R29.2, U1.16, U1.30, U1.31, U1.38, U1.51, U1.61, U1.71, U1.83, U1.94, U1.107, U1.120, U1.130, U1.143, U2.4, U3.3, U3.5, U4.4, U5.2, U5.7, U8.4, U9.2, U11.C, U12.2, U12.3, U13.1, U13.3
NET_U1_6: C13.1, U1.6
NET_U1_25: R4.1, U1.25, U13.4
NET_U1_33: C14.1, C15.1, F1.1, U1.32, U1.33
NET_U1_69: R7.1, U1.69, U4.6
NET_U1_70: R8.1, U1.70, U4.5
NET_U1_136: R5.1, U1.136, U5.6
NET_U1_137: R6.1, U1.137, U5.1
NET_U1_138: R9.1, U1.138
NET_U1_142: U10.3, U10.4
NET_U2_3: R10.1, U2.3
NET_U2_7: R12.1, U2.7
NET_U3_9: R17.1, U3.9
NET_U4_1: R18.1, U4.1
NET_U4_2: R19.1, U4.2
NET_U4_3: R20.1, U4.3
NET_U8_3: R22.1, U8.3
NET_U8_5: R21.1, U8.5
NET_U8_7: R23.2, R24.1, U8.7
NET_U9_1: R26.1, R27.1, U9.1
NET_U9_3: R28.2, R29.1, U9.3
NET_U9_4: R25.1, U9.4, U12.4, U13.2
NET_U10_1: R2.1, U10.1, U10.2
PROC_SPI1_MISO: U1.42, U2.2
PROC_SPI1_MOSI: U1.43, U2.5
PROC_SPI1_NSS: R11.1, U1.40, U2.1
PROC_SPI1_SCK: U1.41, U2.6
PROC_SYS_JTCK_SWCLK: R16.1, U1.109, U3.4
PROC_SYS_JTDI: R14.1, U1.110, U3.8
PROC_SYS_JTDO_TRACESWO: U1.133, U3.6
PROC_SYS_JTMS_SWDIO: R15.1, U1.105, U3.2
RST_OUT_U3_JTAG_RST_B: R13.1, U3.10, U12.1
VCC_S1_15V3: C24.1, C27.1, C28.1, J1.1, R22.2, U8.8
VCC_TIER1_2V5: C1.1, C2.1, C3.1, C4.1, C5.1, C6.1, C7.1, C8.1, C9.1, C10.1, C11.1, C12.1, C20.1, C21.1, C22.1, C23.1, C25.1, C26.1, C29.1, C30.1, F1.2, R4.2, R5.2, R6.2, R7.2, R8.2, R10.2, R11.2, R12.2, R13.2, R14.2, R15.2, R18.2, R21.2, R23.1, R25.2, R26.2, R28.1, U1.17, U1.39, U1.52, U1.62, U1.72, U1.84, U1.95, U1.108, U1.121, U1.131, U1.144, U2.8, U3.1, U4.7, U4.8, U5.5, U8.1, U9.6, U12.5, U13.5
